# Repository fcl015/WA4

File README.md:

# WA4

Plataforma Tecnológica para Riego de Precisión
Se ha desarrollado y validado en campo una plataforma tecnológica para el manejo eficiente en la distribución y el consumo de agua en sistemas de riego agrícola y de áreas verdes. La plataforma ofrece servicios de internet de las cosas, medición, control, predicción y supervisión para una red de riego inteligente capaz de manejar restricciones de infraestructura (agua y energía limitada) valorando las condiciones ambientales (radiación solar, temperatura, lluvia, evapotranspiración) y del cultivo (humedad de suelo, desarrollo vegetativo).  
Actualmente la plataforma se encuentra instalada en una huerta Nogalera y en un invernadero. Experimentalmente, se han obtenido resultados de ahorro de agua entre 30%-40% y de reducción de consumo de energía de entre 20%-30% con respecto a los sistemas de riego automatizados utilizados en la región.
La plataforma consta de tres productos: (1) Crop.Net para monitoreo de humedad de suelo y desarrollo vegetativo, (2) Weather.Net para monitoreo de condiciones ambientales, y (3) Water.Net para control de riego y fertilizantes. Estos productos son modulares y escalables para ajustarse a las necesidades del cliente y al tamaño de las áreas de cultivo.

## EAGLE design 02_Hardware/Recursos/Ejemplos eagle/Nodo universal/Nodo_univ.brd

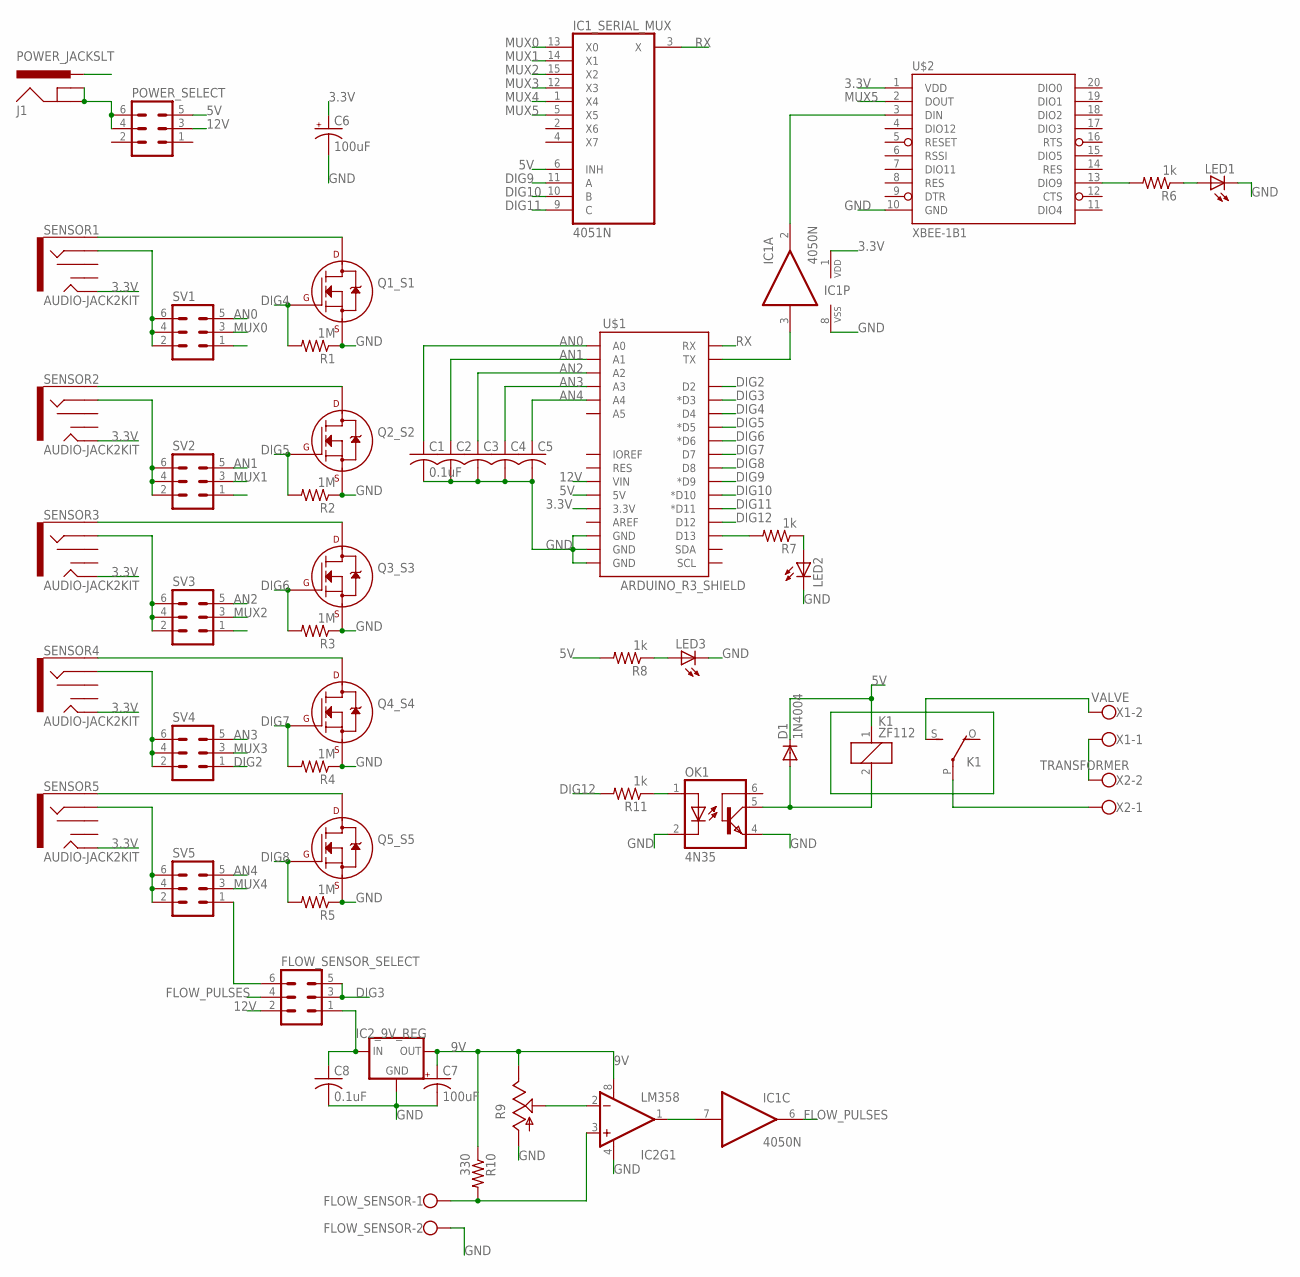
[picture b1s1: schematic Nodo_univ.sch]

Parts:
C1, C8: 0.1uF; C025-025X050
C2, C3, C4, C5: C-US025-025X050; C025-025X050
C6, C7: 100uF; CPOL-RADIAL-100UF-25V
D1: 1N4004; DO41-10
FLOW_SENSOR: W237-102
FLOW_SENSOR_SELECT: MA03-2
IC1: 4050N; DIL16
IC1_SERIAL_MUX: 4051N; DIL16
IC2: LM358; DIP08
IC2_9V_REG: 78XXL
J1: POWER_JACKSLT; POWER_JACK_SLOT
K1: ZF112
LED1, LED2, LED3: LED3MM
OK1: 4N35; DIL06
POWER_SELECT: MA03-2
Q1_S1, Q2_S2, Q3_S3, Q4_S4, Q5_S5: 2N7000_TO92; TO-92
R1, R2, R3, R4, R5: 1M; 0207/10
R6, R7, R8, R11: 1k; 0207/10
R9: TRIM_US-B64Y; B64Y
R10: 330; 0207/10
SENSOR1, SENSOR2, SENSOR3, SENSOR4, SENSOR5: AUDIO-JACK2KIT; AUDIO-JACK-KIT
SV1, SV2, SV3, SV4, SV5: MA03-2
U$1: ARDUINO_R3_SHIELD; UNO_R3_SHIELD
U$2: XBEE-1B1; XBEE-1
X1: VALVE; W237-102
X2: TRANSFORMER; W237-102

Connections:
3.3V: C6.1 (+), IC1.1 (VDD), SENSOR1.TIP, SENSOR2.TIP, SENSOR3.TIP, SENSOR4.TIP, SENSOR5.TIP, U$1.3.3V, U$2.1 (VDD)
5V: D1.C, IC1_SERIAL_MUX.6 (INH), K1.1, POWER_SELECT.5, R8.2, U$1.5V
9V: C7.1 (+), IC2.8 (V+), IC2_9V_REG.OUT, R9.E, R10.1
12V: FLOW_SENSOR_SELECT.2, POWER_SELECT.3, U$1.VIN
AN0: C1.1, SV1.5, U$1.A0
AN1: C2.1, SV2.5, U$1.A1
AN2: C3.1, SV3.5, U$1.A2
AN3: C4.1, SV4.5, U$1.A3
AN4: C5.1, SV5.5, U$1.A4
DIG2: SV4.1, U$1.D2
DIG3: FLOW_SENSOR_SELECT.3, FLOW_SENSOR_SELECT.5, U$1.D3 (*D3)
DIG4: Q1_S1.2 (G), R1.2, U$1.D4
DIG5: Q2_S2.2 (G), R2.2, U$1.D5 (*D5)
DIG6: Q3_S3.2 (G), R3.2, U$1.D6 (*D6)
DIG7: Q4_S4.2 (G), R4.2, U$1.D7
DIG8: Q5_S5.2 (G), R5.2, U$1.D8
DIG9: IC1_SERIAL_MUX.11 (A), U$1.D9 (*D9)
DIG10: IC1_SERIAL_MUX.10 (B), U$1.D10 (*D10)
DIG11: IC1_SERIAL_MUX.9 (C), U$1.D11 (*D11)
DIG12: R11.2, U$1.D12
FLOW_PULSES: FLOW_SENSOR_SELECT.4, IC1.6 (O)
GND: C1.2, C2.2, C3.2, C4.2, C5.2, C6.2 (-), C7.2 (-), C8.2, FLOW_SENSOR.2, IC1.8 (VSS), IC1_SERIAL_MUX.8 (GND), IC2.4 (V-), IC2_9V_REG.GND, J1.PWR, LED1.K (C), LED2.K (C), LED3.K (C), OK1.2 (C), OK1.4 (EMI), Q1_S1.1 (S), Q2_S2.1 (S), Q3_S3.1 (S), Q4_S4.1 (S), Q5_S5.1 (S), R1.1, R2.1, R3.1, R4.1, R5.1, R9.A, U$1.GND@0 (GND), U$1.GND@1 (GND), U$1.GND@2 (GND), U$2.10 (GND)
MUX0: IC1_SERIAL_MUX.13 (X0), SV1.3
MUX1: IC1_SERIAL_MUX.14 (X1), SV2.3
MUX2: IC1_SERIAL_MUX.15 (X2), SV3.3
MUX3: IC1_SERIAL_MUX.12 (X3), SV4.3
MUX4: IC1_SERIAL_MUX.1 (X4), SV5.3
MUX5: IC1_SERIAL_MUX.5 (X5), U$2.2 (DOUT)
unnamed: Q1_S1.3 (D), SENSOR1.SLEEVE
unnamed: Q2_S2.3 (D), SENSOR2.SLEEVE
unnamed: Q3_S3.3 (D), SENSOR3.SLEEVE
unnamed: Q4_S4.3 (D), SENSOR4.SLEEVE
unnamed: Q5_S5.3 (D), SENSOR5.SLEEVE
unnamed: SENSOR1.RING, SV1.2, SV1.4, SV1.6
unnamed: SENSOR2.RING, SV2.2, SV2.4, SV2.6
unnamed: SENSOR3.RING, SV3.2, SV3.4, SV3.6
unnamed: SENSOR4.RING, SV4.2, SV4.4, SV4.6
unnamed: SENSOR5.RING, SV5.2, SV5.4, SV5.6
unnamed: FLOW_SENSOR_SELECT.6, SV5.1
unnamed: IC1.3 (I), U$1.TX
unnamed: IC1.2 (O), U$2.3 (DIN)
unnamed: R6.2, U$2.13 (DIO9)
unnamed: LED1.A, R6.1
unnamed: R7.2, U$1.D13
unnamed: LED2.A, R7.1
unnamed: C8.1, FLOW_SENSOR_SELECT.1, IC2_9V_REG.IN
unnamed: IC2.2 (-IN), R9.S
unnamed: LED3.A, R8.1
unnamed: J1.GND@1 (GNDBREAK), J1.GND@2 (GND), POWER_SELECT.4, POWER_SELECT.6
unnamed: IC1.7 (I), IC2.1 (OUT)
unnamed: FLOW_SENSOR.1, IC2.3 (+IN), R10.2
unnamed: OK1.1 (A), R11.1
unnamed: D1.A, K1.2, OK1.5 (COL)
unnamed: X1.1, X2.2
unnamed: K1.P, X2.1
unnamed: K1.S, X1.2
RX: IC1_SERIAL_MUX.3 (X), U$1.RX
VCC: IC1_SERIAL_MUX.16 (VCC)
VEE: IC1_SERIAL_MUX.7 (VEE)

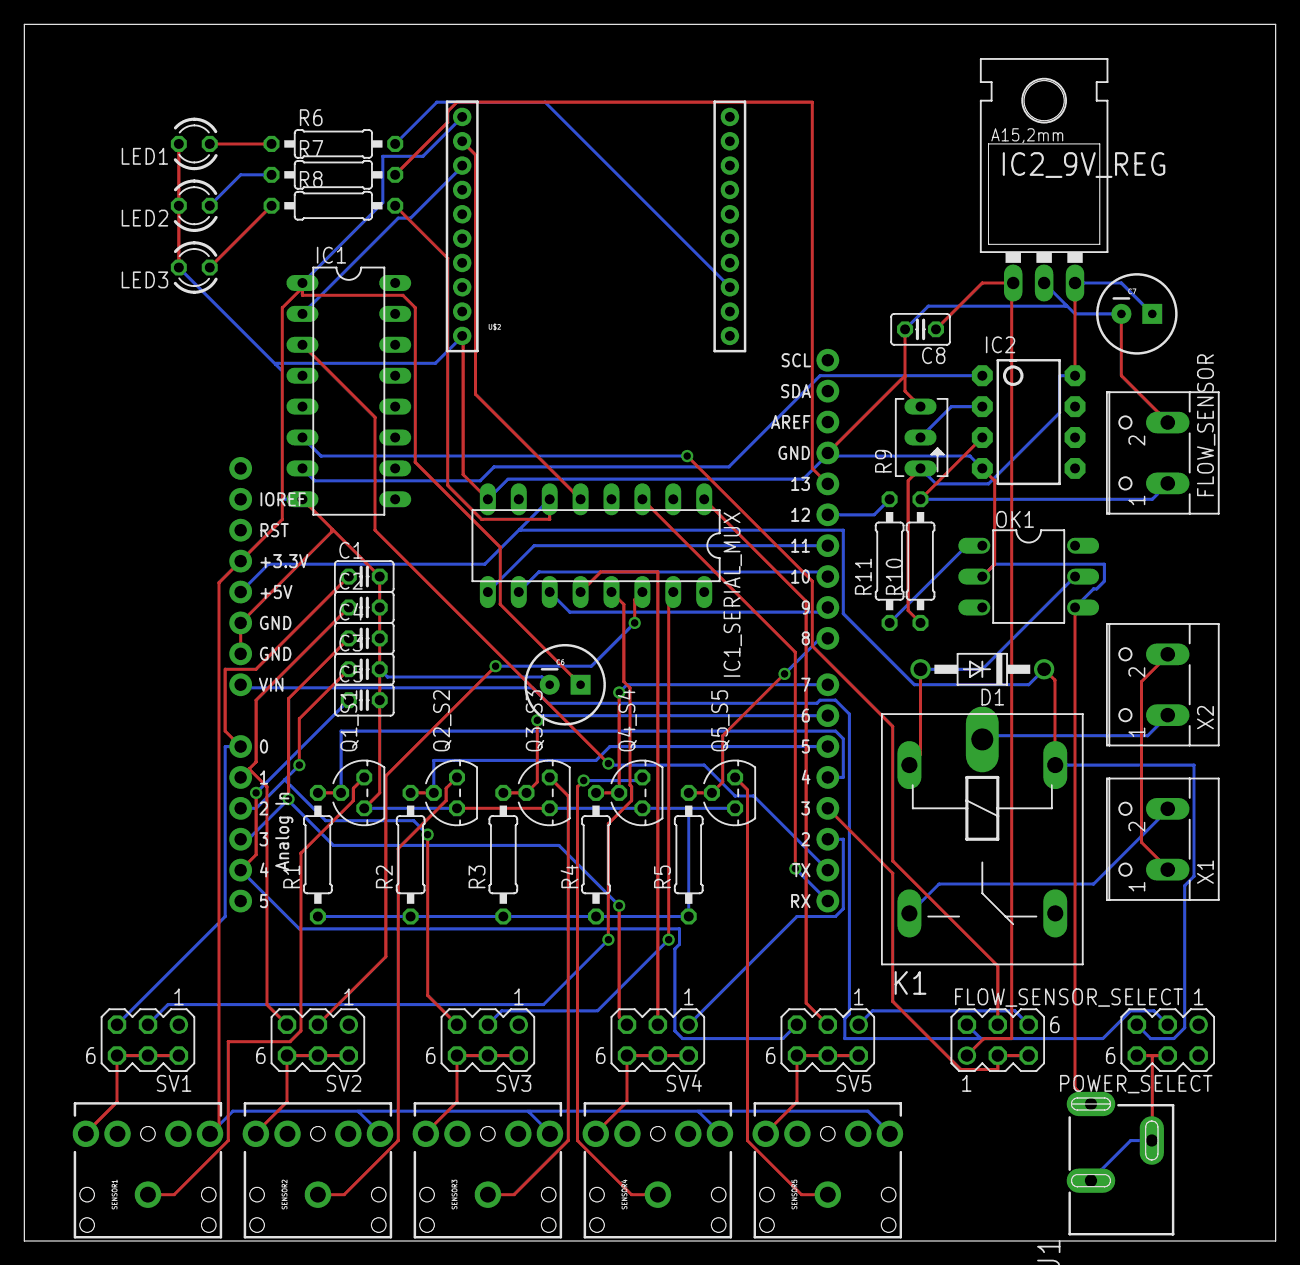
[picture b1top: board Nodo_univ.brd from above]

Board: 2 copper layers, 102.9 x 100.0 mm, 52 parts (0 on the bottom side), 57 nets.

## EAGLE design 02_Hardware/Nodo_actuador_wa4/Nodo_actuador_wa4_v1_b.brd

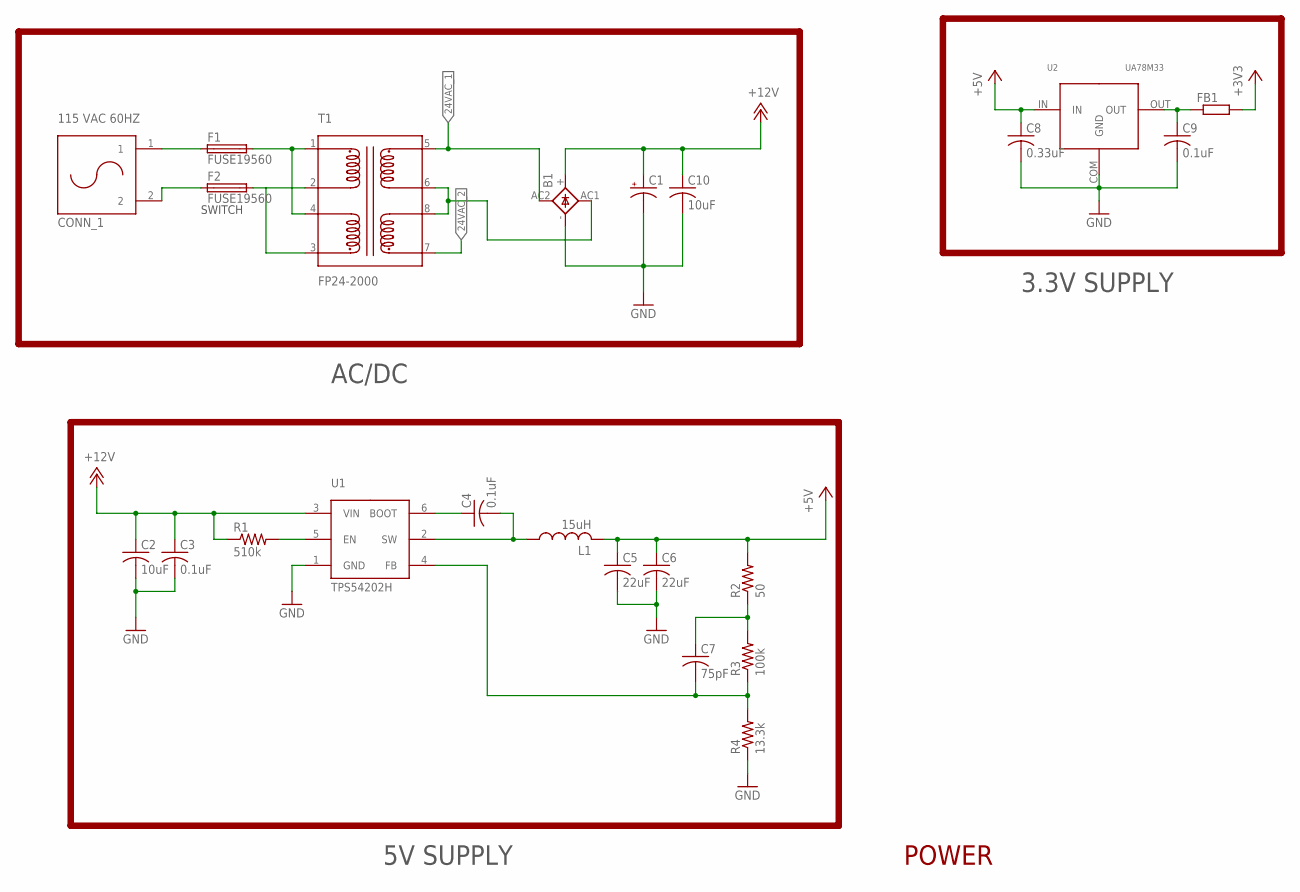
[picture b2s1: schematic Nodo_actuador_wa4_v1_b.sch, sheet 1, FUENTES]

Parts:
B1: GBU4; GBU4S
C1: CPOL-USE5-13; E5-13
C2, C10: 10uF; C0805
C3, C4, C9: 0.1uF; C0805
C5, C6: 22uF; C0805
C7: 75pF; C0805
C8: 0.33uF; C0805
CONN_1: 115 VAC 60HZ; 2570-2210
F1, F2: FUSE19560; 19560
FB1: R-EU_M0805; M0805
L1: 15uH; VLS5045
R1: 510k; R0805
R2: 50; R0805
R3: 100k; R0805
R4: 13.3k; R0805
T1: FP24-2000
U1: TPS54202H; SOT-23-6
U2: UA78M33; UA78XX

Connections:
24VAC_1: B1.AC2 (AC1), T1.5; also elsewhere on the board
24VAC_2: T1.7; also elsewhere on the board
+3V3: FB1.2; also elsewhere on the board
+5V: C5.1, C6.1, C8.1, L1.2, R2.2, U2.IN; also elsewhere on the board
+12V: B1.+, C1.+, C2.1, C3.1, C10.1, R1.1, U1.3 (VIN); also elsewhere on the board
GND: B1.-, C1.-, C2.2, C3.2, C5.2, C6.2, C8.2, C9.2, C10.2, R4.1, U1.1 (GND), U2.COM (GND); also elsewhere on the board
unnamed: F1.2, T1.1, T1.4
unnamed: F2.2, T1.2, T1.3
unnamed: B1.AC1 (AC2), T1.6, T1.8
unnamed: C4.1, U1.6 (BOOT)
unnamed: C4.2, L1.1, U1.2 (SW)
unnamed: R1.2, U1.5 (EN)
unnamed: C7.1, R2.1, R3.2
unnamed: C7.2, R3.1, R4.2, U1.4 (FB)
unnamed: CONN_1.1, F1.1
unnamed: CONN_1.2, F2.1
unnamed: C9.1, FB1.1, U2.OUT

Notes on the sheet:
POWER
5V SUPPLY
3.3V SUPPLY
AC/DC
SWITCH

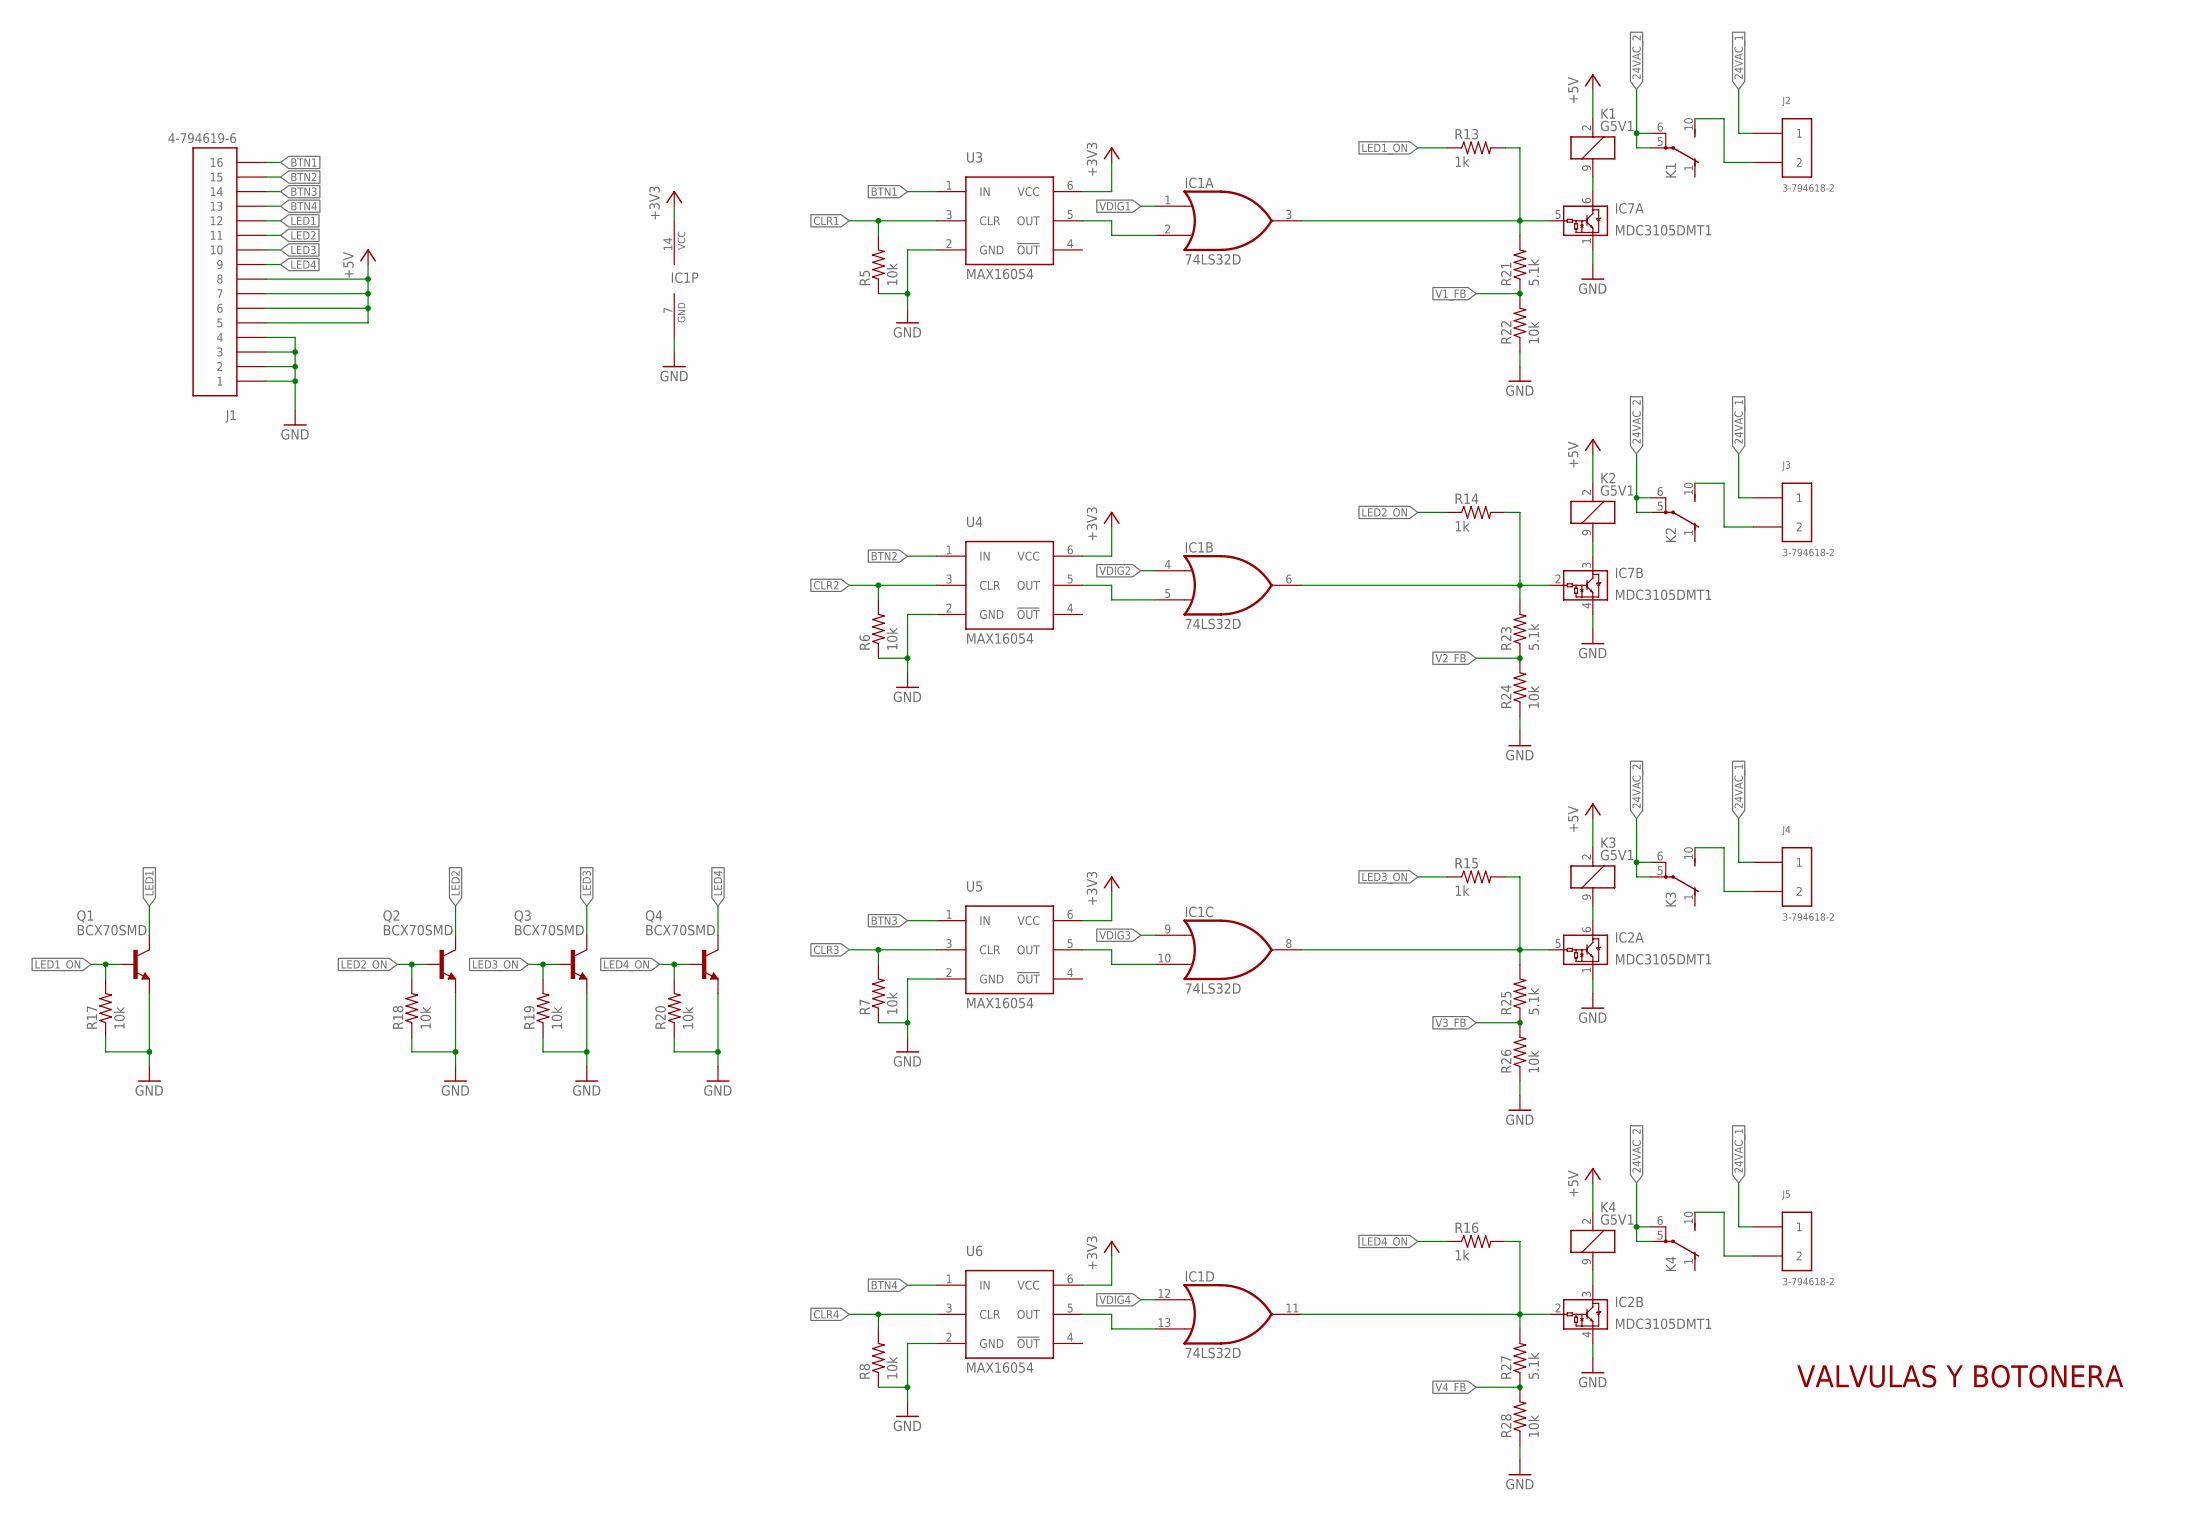
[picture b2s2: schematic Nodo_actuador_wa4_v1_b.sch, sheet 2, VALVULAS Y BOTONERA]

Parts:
IC1: 74LS32D; SO14
IC2, IC7: MDC3105DMT1; SC-74
J1: 4-794619-6
J2, J3, J4, J5: 3-794618-2
K1, K2, K3, K4: G5V1
Q1, Q2, Q3, Q4: BCX70SMD; SOT23
R5, R6, R7, R8, R17, R18, R19, R20, R22, R24, R26, R28: 10k; R0805
R13, R14, R15, R16: 1k; R0805
R21, R23, R25, R27: 5.1k; R0805
U3, U4, U5, U6: MAX16054; SOT-23-6

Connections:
24VAC_1: J2.1, J3.1, J4.1, J5.1; also elsewhere on the board
24VAC_2: K1.5, K1.6, K2.5, K2.6, K3.5, K3.6, K4.5, K4.6; also elsewhere on the board
+3V3: IC1.14 (VCC), U3.6 (VCC), U4.6 (VCC), U5.6 (VCC), U6.6 (VCC); also elsewhere on the board
+5V: J1.5, J1.6, J1.7, J1.8, K1.2 (1), K2.2 (1), K3.2 (1), K4.2 (1); also elsewhere on the board
BTN1: J1.16, U3.1 (IN)
BTN2: J1.15, U4.1 (IN)
BTN3: J1.14, U5.1 (IN)
BTN4: J1.13, U6.1 (IN)
CLR1: R5.2, U3.3 (CLR); also elsewhere on the board
CLR2: R6.2, U4.3 (CLR); also elsewhere on the board
CLR3: R7.2, U5.3 (CLR); also elsewhere on the board
CLR4: R8.2, U6.3 (CLR); also elsewhere on the board
GND: IC1.7 (GND), IC2.1 (GND), IC2.4 (GND), IC7.1 (GND), IC7.4 (GND), J1.1, J1.2, J1.3, J1.4, Q1.2 (E), Q2.2 (E), Q3.2 (E), Q4.2 (E), R5.1, R6.1, R7.1, R8.1, R17.1, R18.1, R19.1, R20.1, R22.1, R24.1, R26.1, R28.1, U3.2 (GND), U4.2 (GND), U5.2 (GND), U6.2 (GND); also elsewhere on the board
LED1: J1.12, Q1.3 (C)
LED1_ON: Q1.1 (B), R13.1, R17.2
LED2: J1.11, Q2.3 (C)
LED2_ON: Q2.1 (B), R14.1, R18.2
LED3: J1.10, Q3.3 (C)
LED3_ON: Q3.1 (B), R15.1, R19.2
LED4: J1.9, Q4.3 (C)
LED4_ON: Q4.1 (B), R16.1, R20.2
unnamed: IC1.2 (I1), U3.5 (OUT)
unnamed: IC1.5 (I1), U4.5 (OUT)
unnamed: IC1.10 (I1), U5.5 (OUT)
unnamed: IC1.13 (I1), U6.5 (OUT)
unnamed: IC1.3 (O), IC7.5 (VIN), R13.2, R21.2
unnamed: IC7.6 (VOUT), K1.9 (2)
unnamed: IC7.3 (VOUT), K2.9 (2)
unnamed: IC1.8 (O), IC2.5 (VIN), R15.2, R25.2
unnamed: IC2.6 (VOUT), K3.9 (2)
unnamed: IC1.11 (O), IC2.2 (VIN), R16.2, R27.2
unnamed: IC2.3 (VOUT), K4.9 (2)
unnamed: J2.2, K1.10 (S)
unnamed: J3.2, K2.10 (S)
unnamed: J4.2, K3.10 (S)
unnamed: J5.2, K4.10 (S)
unnamed: IC1.6 (O), IC7.2 (VIN), R14.2, R23.2
V1_FB: R21.1, R22.2; also elsewhere on the board
V2_FB: R23.1, R24.2; also elsewhere on the board
V3_FB: R25.1, R26.2; also elsewhere on the board
V4_FB: R27.1, R28.2; also elsewhere on the board
VDIG1: IC1.1 (I0); also elsewhere on the board
VDIG2: IC1.4 (I0); also elsewhere on the board
VDIG3: IC1.9 (I0); also elsewhere on the board
VDIG4: IC1.12 (I0); also elsewhere on the board

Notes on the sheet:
VALVULAS Y BOTONERA

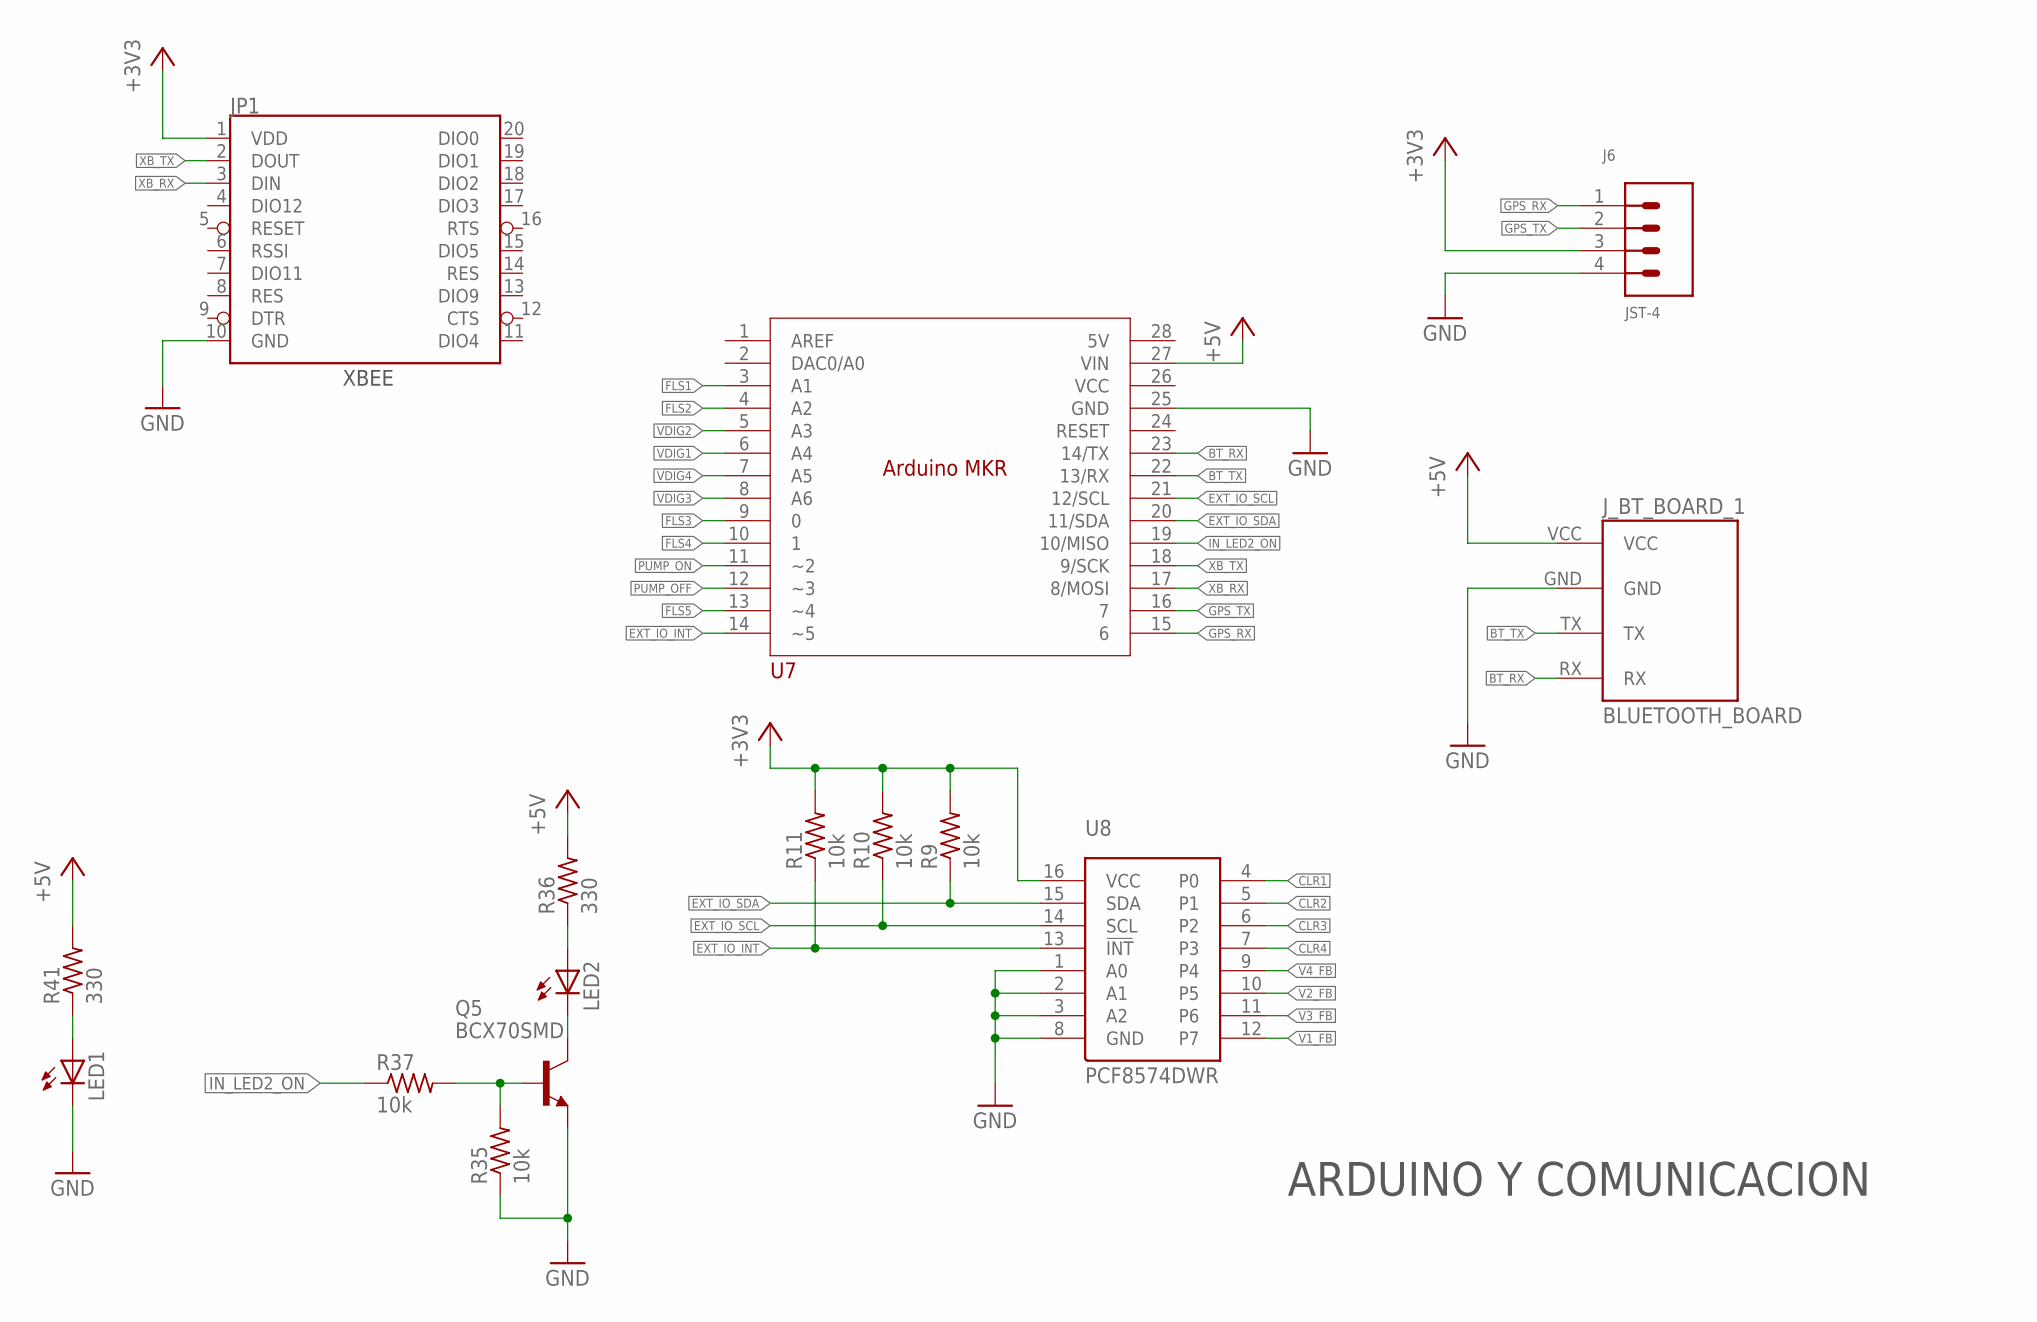
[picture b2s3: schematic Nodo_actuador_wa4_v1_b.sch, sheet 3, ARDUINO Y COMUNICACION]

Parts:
J6: JST-4
JP1: XBEESILK; XBEE-SILK
J_BT_BOARD_1: BLUETOOTH_BOARD; BT_BOARD_FOOTPRINT
LED1, LED2: LEDCHIP-LED0805; CHIP-LED0805
Q5: BCX70SMD; SOT23
R9, R10, R11, R35, R37: 10k; R0805
R36, R41: 330; R0805
U7: ARDUINO_MKR
U8: PCF8574DWR; SOIC16_1

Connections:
+3V3: J6.3, JP1.1 (VDD), R9.2, R10.2, R11.2, U8.16 (VCC); also elsewhere on the board
+5V: J_BT_BOARD_1.VCC, R36.2, R41.2, U7.27 (VIN); also elsewhere on the board
BT_RX: J_BT_BOARD_1.RX, U7.23 (14/TX)
BT_TX: J_BT_BOARD_1.TX, U7.22 (13/RX)
CLR1: U8.4 (P0); also elsewhere on the board
CLR2: U8.5 (P1); also elsewhere on the board
CLR3: U8.6 (P2); also elsewhere on the board
CLR4: U8.7 (P3); also elsewhere on the board
EXT_IO_INT: R11.1, U7.14 (~5), U8.13 (!INT)
EXT_IO_SCL: R10.1, U7.21 (12/SCL), U8.14 (SCL)
EXT_IO_SDA: R9.1, U7.20 (11/SDA), U8.15 (SDA)
FLS1: U7.3 (A1); also elsewhere on the board
FLS2: U7.4 (A2); also elsewhere on the board
FLS3: U7.9 (0); also elsewhere on the board
FLS4: U7.10 (1); also elsewhere on the board
FLS5: U7.13 (~4); also elsewhere on the board
GND: J6.4, JP1.10 (GND), J_BT_BOARD_1.GND, LED1.C, Q5.2 (E), R35.1, U7.25 (GND), U8.1 (A0), U8.2 (A1), U8.3 (A2), U8.8 (GND); also elsewhere on the board
GPS_RX: J6.1, U7.15 (6)
GPS_TX: J6.2, U7.16 (7)
IN_LED2_ON: R37.1, U7.19 (10/MISO)
unnamed: LED2.A, R36.1
unnamed: LED2.C, Q5.3 (C)
unnamed: LED1.A, R41.1
unnamed: Q5.1 (B), R35.2, R37.2
PUMP_OFF: U7.12 (~3); also elsewhere on the board
PUMP_ON: U7.11 (~2); also elsewhere on the board
V1_FB: U8.12 (P7); also elsewhere on the board
V2_FB: U8.10 (P5); also elsewhere on the board
V3_FB: U8.11 (P6); also elsewhere on the board
V4_FB: U8.9 (P4); also elsewhere on the board
VDIG1: U7.6 (A4); also elsewhere on the board
VDIG2: U7.5 (A3); also elsewhere on the board
VDIG3: U7.8 (A6); also elsewhere on the board
VDIG4: U7.7 (A5); also elsewhere on the board
XB_RX: JP1.3 (DIN), U7.17 (8/MOSI)
XB_TX: JP1.2 (DOUT), U7.18 (9/SCK)

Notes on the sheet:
ARDUINO Y COMUNICACION
XBEE

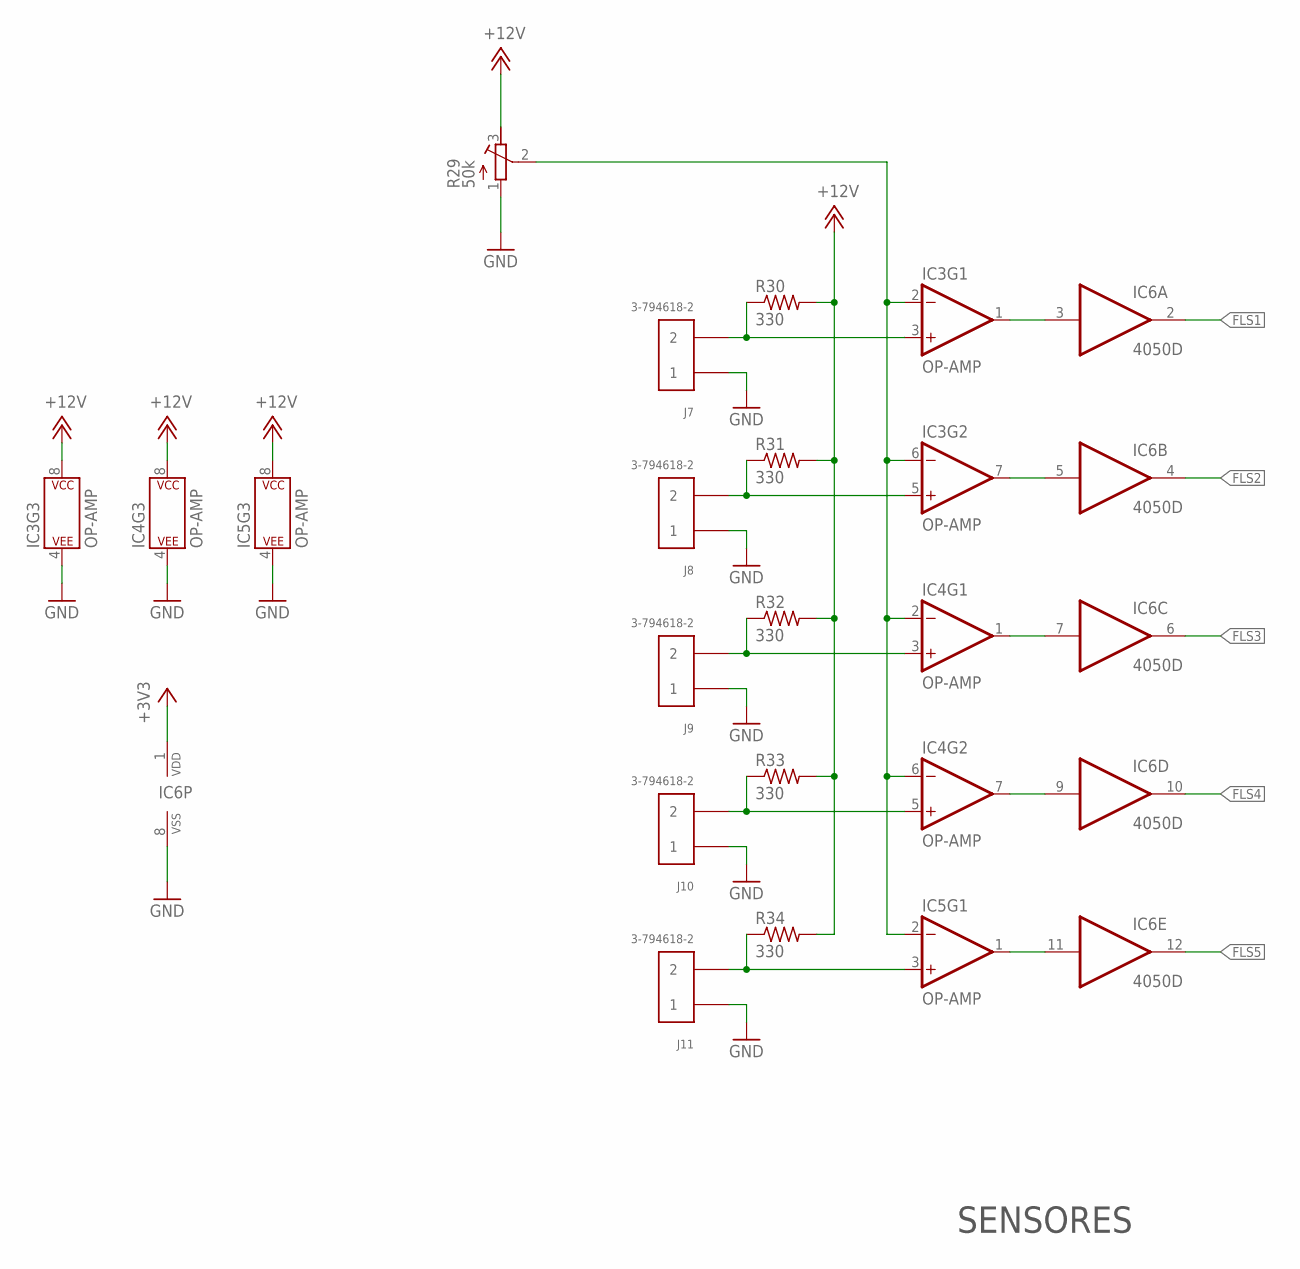
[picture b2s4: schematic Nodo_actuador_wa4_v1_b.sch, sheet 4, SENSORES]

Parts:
IC3, IC4, IC5: OP-AMP; SO08
IC6: 4050D; SO16
J7, J8, J9, J10, J11: 3-794618-2
R29: 50k; RTRIM3224W
R30, R31, R32, R33, R34: 330; R0805

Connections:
+3V3: IC6.1 (VDD); also elsewhere on the board
+12V: IC3.8 (P$V+), IC4.8 (P$V+), IC5.8 (P$V+), R29.3 (E), R30.2, R31.2, R32.2, R33.2, R34.2; also elsewhere on the board
FLS1: IC6.2 (O); also elsewhere on the board
FLS2: IC6.4 (O); also elsewhere on the board
FLS3: IC6.6 (O); also elsewhere on the board
FLS4: IC6.10 (O); also elsewhere on the board
FLS5: IC6.12 (O); also elsewhere on the board
GND: IC3.4 (P$V-), IC4.4 (P$V-), IC5.4 (P$V-), IC6.8 (VSS), J7.1, J8.1, J9.1, J10.1, J11.1, R29.1 (A); also elsewhere on the board
unnamed: IC3.3 (+IN), J7.2, R30.1
unnamed: IC3.5 (+IN), J8.2, R31.1
unnamed: IC4.3 (+IN), J9.2, R32.1
unnamed: IC4.5 (+IN), J10.2, R33.1
unnamed: IC5.3 (+IN), J11.2, R34.1
unnamed: IC3.1 (OUT), IC6.3 (I)
unnamed: IC3.7 (OUT), IC6.5 (I)
unnamed: IC4.1 (OUT), IC6.7 (I)
unnamed: IC4.7 (OUT), IC6.9 (I)
unnamed: IC5.1 (OUT), IC6.11 (I)
SENSOR_VREF: IC3.2 (-IN), IC3.6 (-IN), IC4.2 (-IN), IC4.6 (-IN), IC5.2 (-IN), R29.2 (S)

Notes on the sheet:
SENSORES

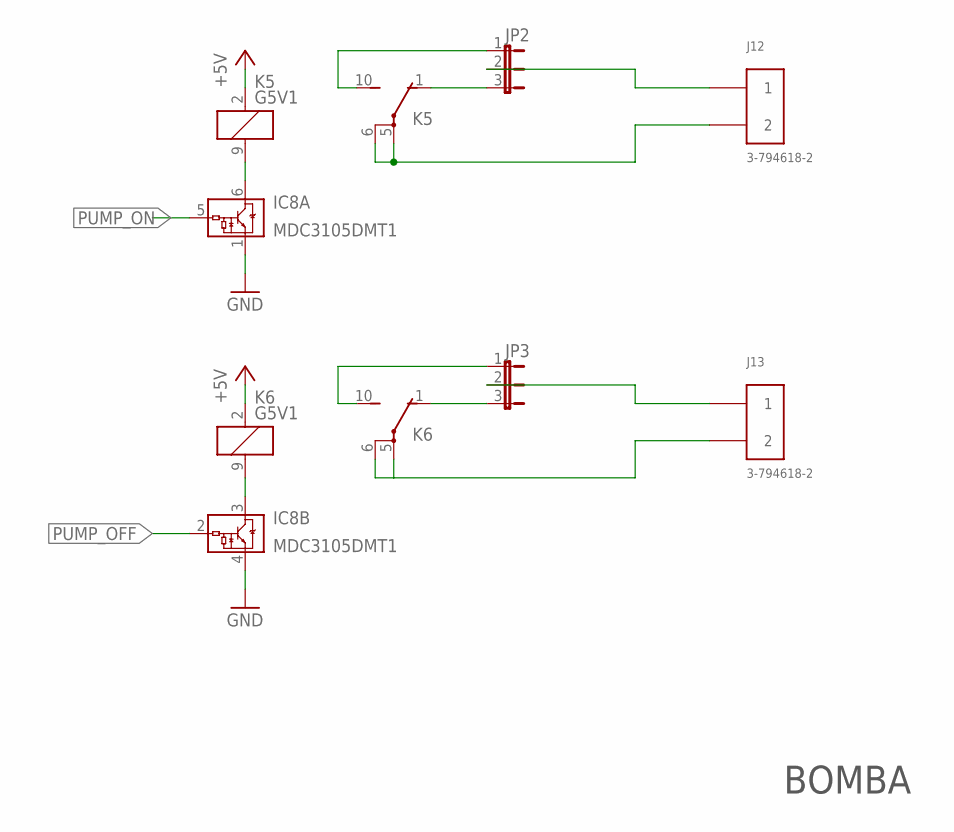
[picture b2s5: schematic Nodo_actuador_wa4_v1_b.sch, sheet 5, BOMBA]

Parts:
IC8: MDC3105DMT1; SC-74
J12, J13: 3-794618-2
JP2, JP3: JP2E; JP2
K5, K6: G5V1

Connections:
+5V: K5.2 (1), K6.2 (1); also elsewhere on the board
GND: IC8.1 (GND), IC8.4 (GND); also elsewhere on the board
unnamed: IC8.6 (VOUT), K5.9 (2)
unnamed: JP2.1, K5.10 (S)
unnamed: JP2.3, K5.1 (O)
unnamed: J12.1, JP2.2
unnamed: J12.2, K5.5, K5.6
unnamed: J13.1, JP3.2
unnamed: J13.2, K6.5, K6.6
unnamed: JP3.1, K6.10 (S)
unnamed: JP3.3, K6.1 (O)
unnamed: IC8.3 (VOUT), K6.9 (2)
PUMP_OFF: IC8.2 (VIN); also elsewhere on the board
PUMP_ON: IC8.5 (VIN); also elsewhere on the board

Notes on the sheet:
BOMBA

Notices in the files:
parts and their libraries:
SparkFun-RF: Licensing: Creative Commons ShareAlike 4.0 International - https://creativecommons.org/licenses/by-sa/4.0
sf-bluegiga: Package design from "pretty-eagle-libs" at https://github.com/esden/pretty-eagle-libs/blob/master/pel_misc.lbr by @esden at Github. (CC-BY-SA-3.0)
